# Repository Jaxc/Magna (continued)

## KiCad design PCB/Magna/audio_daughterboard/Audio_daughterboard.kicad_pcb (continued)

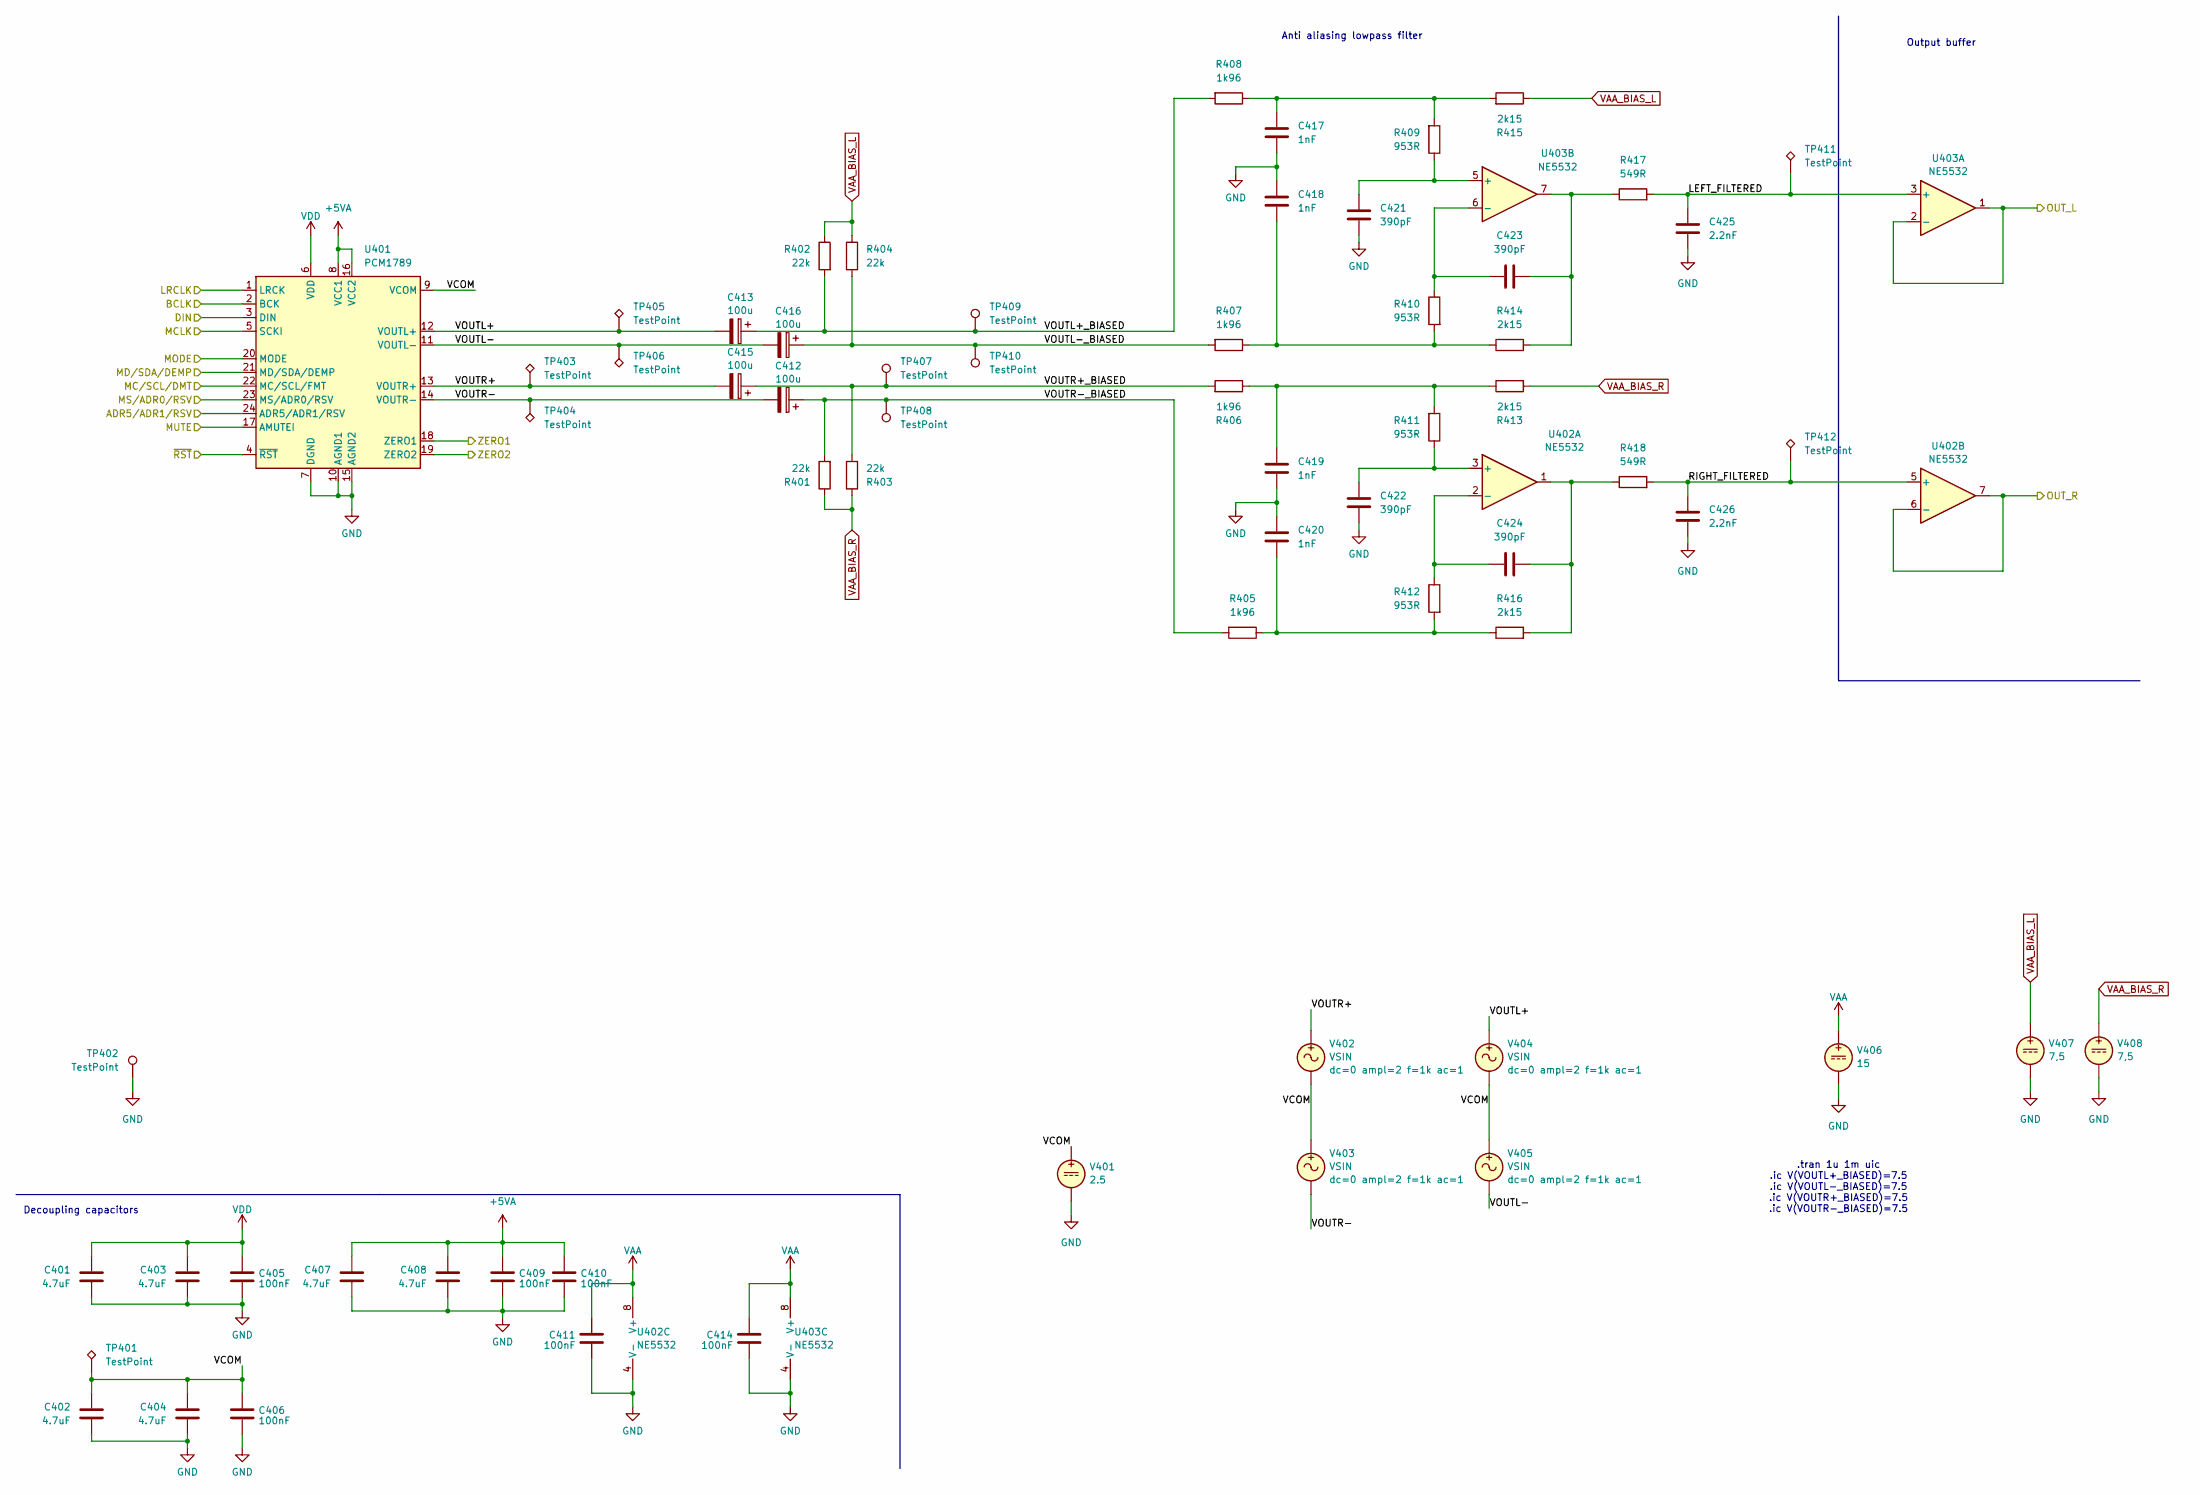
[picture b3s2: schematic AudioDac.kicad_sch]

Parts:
C401, C402, C403, C404, C407, C408: 4.7uF; C_1206_3216Metric; LCSC C29823
C405, C406, C409, C410, C411, C414: 100nF; C_0603_1608Metric; LCSC C14663
C412, C413, C415, C416: 100u; CP_Elec_6.3x7.7; LCSC C251007
C417, C418, C419, C420: 1nF; C_0603_1608Metric; LCSC C163508
C421, C422, C423, C424: 390pF; C_0603_1608Metric; LCSC C472793
C425, C426: 2.2nF; C_0603_1608Metric; LCSC C33353
R401, R402, R403, R404: 22k; R_0603_1608Metric; LCSC C335085
R405, R406, R407, R408: 1k96; R_0603_1608Metric; LCSC C160602
R409, R410, R411, R412: 953R; R_0603_1608Metric; LCSC C311896
R413, R414, R415, R416: 2k15; R_0603_1608Metric; LCSC C667562
R417, R418: 549R; R_0603_1608Metric; LCSC C218072
TP401, TP403, TP404, TP405, TP406, TP411, TP412: TestPoint; TestPoint_Pad_1.0x1.0mm
TP402, TP407, TP408, TP409, TP410: TestPoint; TestPoint_Keystone_5005-5009_Compact
U401: PCM1789; TSSOP-24_4.4x7.8mm_P0.65mm; LCSC C962089
U402, U403: NE5532; SOIC-8_3.9x4.9mm_P1.27mm; LCSC C7426
V401: 2.5
V402, V403, V404, V405: VSIN
V406: 15
V407, V408: 7,5

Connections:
+5VA: C407.1, C408.1, C409.1, C410.1, U401.8 (VCC1), U401.16 (VCC2); also elsewhere on the board
/AudioDac0/ADR5/ADR1/RSV: U401.24 (ADR5/ADR1/RSV); also elsewhere on the board
/AudioDac0/LEFT_FILTERED: C425.2, R417.2, TP411.1, U403.3 (+)
/AudioDac0/MC/SCL/DMT: U401.22 (MC/SCL/FMT); also elsewhere on the board
/AudioDac0/MD/SDA/DEMP: U401.21 (MD/SDA/DEMP); also elsewhere on the board
/AudioDac0/MODE: U401.20 (MODE); also elsewhere on the board
/AudioDac0/MS/ADR0/RSV: U401.23 (MS/ADR0/RSV); also elsewhere on the board
/AudioDac0/MUTE: U401.17 (AMUTEI); also elsewhere on the board
/AudioDac0/OUT_L: U403.1, U403.2 (-); also elsewhere on the board
/AudioDac0/OUT_R: U402.6 (-), U402.7; also elsewhere on the board
/AudioDac0/RIGHT_FILTERED: C426.2, R418.2, TP412.1, U402.5 (+)
/AudioDac0/VCOM: C402.1, C404.1, C406.1, TP401.1, U401.9 (VCOM)
/AudioDac0/VOUTL+: C413.2, TP405.1, U401.12 (VOUTL+)
/AudioDac0/VOUTL+_BIASED: C413.1, R402.2, R408.2, TP409.1
/AudioDac0/VOUTL-: C416.2, TP406.1, U401.11 (VOUTL-)
/AudioDac0/VOUTL-_BIASED: C416.1, R404.2, R407.2, TP410.1
/AudioDac0/VOUTR+: C415.2, TP403.1, U401.13 (VOUTR+)
/AudioDac0/VOUTR+_BIASED: C415.1, R403.2, R406.2, TP407.1
/AudioDac0/VOUTR-: C412.2, TP404.1, U401.14 (VOUTR-)
/AudioDac0/VOUTR-_BIASED: C412.1, R401.2, R405.2, TP408.1
/AudioDac0/ZERO1: U401.18 (ZERO1); also elsewhere on the board
/AudioDac0/ZERO2: U401.19 (ZERO2); also elsewhere on the board
/AudioDac0/~RST: U401.4 (~RST); also elsewhere on the board
/DAC1_BCLK: U401.2 (BCK); also elsewhere on the board
/DAC1_MCLK: U401.5 (SCKI); also elsewhere on the board
/DAC_DATA_1: U401.3 (DIN); also elsewhere on the board
/LRCLK: U401.1 (LRCK); also elsewhere on the board
GND: C401.2, C402.2, C403.2, C404.2, C405.2, C406.2, C407.2, C408.2, C409.2, C410.2, C411.2, C414.2, C417.2, C418.1, C419.2, C420.1, C421.2, C422.2, C425.1, C426.1, TP402.1, U401.7 (DGND), U401.10 (AGND1), U401.15 (AGND2), U402.4 (V-), U403.4 (V-), V401.2, V406.2, V407.2, V408.2; also elsewhere on the board
unnamed: C417.1, R408.1, R409.2, R415.2
unnamed: C418.2, R407.1, R410.2, R414.1
unnamed: C419.1, R406.1, R411.2, R413.1
unnamed: C420.2, R405.1, R412.2, R416.1
unnamed: C423.2, R414.2, R417.1, U403.7
unnamed: C424.2, R416.2, R418.1, U402.1
unnamed: C422.1, R411.1, U402.3 (+)
unnamed: C424.1, R412.1, U402.2 (-)
unnamed: C421.1, R409.1, U403.5 (+)
unnamed: C423.1, R410.1, U403.6 (-)
VAA: C411.1, C414.1, U402.8 (V+), U403.8 (V+), V406.1; also elsewhere on the board
VAA_BIAS_L: R402.1, R404.1, R415.1, V407.1; also elsewhere on the board
VAA_BIAS_R: R401.1, R403.1, R413.2, V408.1; also elsewhere on the board
VDD: C401.1, C403.1, C405.1, U401.6 (VDD); also elsewhere on the board

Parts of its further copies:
C501, C502, C503, C504, C507, C508: 4.7uF; C_1206_3216Metric; LCSC C29823
C505, C506, C509, C510, C511, C514: 100nF; C_0603_1608Metric; LCSC C14663
C512, C513, C515, C516: 100u; CP_Elec_6.3x7.7; LCSC C251007
C517, C518, C519, C520: 1nF; C_0603_1608Metric; LCSC C163508
C521, C522, C523, C524: 390pF; C_0603_1608Metric; LCSC C472793
C525, C526: 2.2nF; C_0603_1608Metric; LCSC C33353
R501, R502, R503, R504: 22k; R_0603_1608Metric; LCSC C335085
R505, R506, R507, R508: 1k96; R_0603_1608Metric; LCSC C160602
R509, R510, R511, R512: 953R; R_0603_1608Metric; LCSC C311896
R513, R514, R515, R516: 2k15; R_0603_1608Metric; LCSC C667562
R517, R518: 549R; R_0603_1608Metric; LCSC C218072
TP501, TP503, TP504, TP505, TP506, TP511, TP512: TestPoint; TestPoint_Pad_1.0x1.0mm
TP502, TP507, TP508, TP509, TP510: TestPoint; TestPoint_Keystone_5005-5009_Compact
U501: PCM1789; TSSOP-24_4.4x7.8mm_P0.65mm; LCSC C962089
U502, U503: NE5532; SOIC-8_3.9x4.9mm_P1.27mm; LCSC C7426

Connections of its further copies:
+5VA: C507.1, C508.1, C509.1, C510.1, U501.8 (VCC1), U501.16 (VCC2); also elsewhere on the board
/AudioDac0/MC/SCL/DMT: U501.22 (MC/SCL/FMT); also elsewhere on the board
/AudioDac0/MD/SDA/DEMP: U501.21 (MD/SDA/DEMP); also elsewhere on the board
/AudioDac0/MUTE: U501.17 (AMUTEI); also elsewhere on the board
/AudioDac0/~RST: U501.4 (~RST); also elsewhere on the board
/AudioDac1/ADR5/ADR1/RSV: U501.24 (ADR5/ADR1/RSV); also elsewhere on the board
/AudioDac1/LEFT_FILTERED: C525.2, R517.2, TP511.1, U503.3 (+)
/AudioDac1/MODE: U501.20 (MODE); also elsewhere on the board
/AudioDac1/MS/ADR0/RSV: U501.23 (MS/ADR0/RSV); also elsewhere on the board
/AudioDac1/OUT_L: U503.1, U503.2 (-); also elsewhere on the board
/AudioDac1/OUT_R: U502.6 (-), U502.7; also elsewhere on the board
/AudioDac1/RIGHT_FILTERED: C526.2, R518.2, TP512.1, U502.5 (+)
/AudioDac1/VCOM: C502.1, C504.1, C506.1, TP501.1, U501.9 (VCOM)
/AudioDac1/VOUTL+: C513.2, TP505.1, U501.12 (VOUTL+)
/AudioDac1/VOUTL+_BIASED: C513.1, R502.2, R508.2, TP509.1
/AudioDac1/VOUTL-: C516.2, TP506.1, U501.11 (VOUTL-)
/AudioDac1/VOUTL-_BIASED: C516.1, R504.2, R507.2, TP510.1
/AudioDac1/VOUTR+: C515.2, TP503.1, U501.13 (VOUTR+)
/AudioDac1/VOUTR+_BIASED: C515.1, R503.2, R506.2, TP507.1
/AudioDac1/VOUTR-: C512.2, TP504.1, U501.14 (VOUTR-)
/AudioDac1/VOUTR-_BIASED: C512.1, R501.2, R505.2, TP508.1
/AudioDac1/ZERO1: U501.18 (ZERO1); also elsewhere on the board
/AudioDac1/ZERO2: U501.19 (ZERO2); also elsewhere on the board
/DAC0_BCLK: U501.2 (BCK); also elsewhere on the board
/DAC0_MCLK: U501.5 (SCKI); also elsewhere on the board
/DAC_DATA_0: U501.3 (DIN); also elsewhere on the board
/LRCLK: U501.1 (LRCK); also elsewhere on the board
GND: C501.2, C502.2, C503.2, C504.2, C505.2, C506.2, C507.2, C508.2, C509.2, C510.2, C511.2, C514.2, C517.2, C518.1, C519.2, C520.1, C521.2, C522.2, C525.1, C526.1, TP502.1, U501.7 (DGND), U501.10 (AGND1), U501.15 (AGND2), U502.4 (V-), U503.4 (V-); also elsewhere on the board
unnamed: C517.1, R508.1, R509.2, R515.2
unnamed: C518.2, R507.1, R510.2, R514.1
unnamed: C519.1, R506.1, R511.2, R513.1
unnamed: C520.2, R505.1, R512.2, R516.1
unnamed: C523.2, R514.2, R517.1, U503.7
unnamed: C524.2, R516.2, R518.1, U502.1
unnamed: C522.1, R511.1, U502.3 (+)
unnamed: C524.1, R512.1, U502.2 (-)
unnamed: C521.1, R509.1, U503.5 (+)
unnamed: C523.1, R510.1, U503.6 (-)
VAA: C511.1, C514.1, U502.8 (V+), U503.8 (V+); also elsewhere on the board
VAA_BIAS_L: R502.1, R504.1, R515.1; also elsewhere on the board
VAA_BIAS_R: R501.1, R503.1, R513.2; also elsewhere on the board
VDD: C501.1, C503.1, C505.1, U501.6 (VDD); also elsewhere on the board

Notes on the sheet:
Decoupling capacitors
Output buffer
.tran 1u 1m uic .ic V(VOUTL+_BIASED)=7.5 .ic V(VOUTL-_BIASED)=7.5 .ic V(VOUTR+_BIASED)=7.5 .ic V(VOUTR-_BIASED)=7.5
Anti aliasing lowpass filter

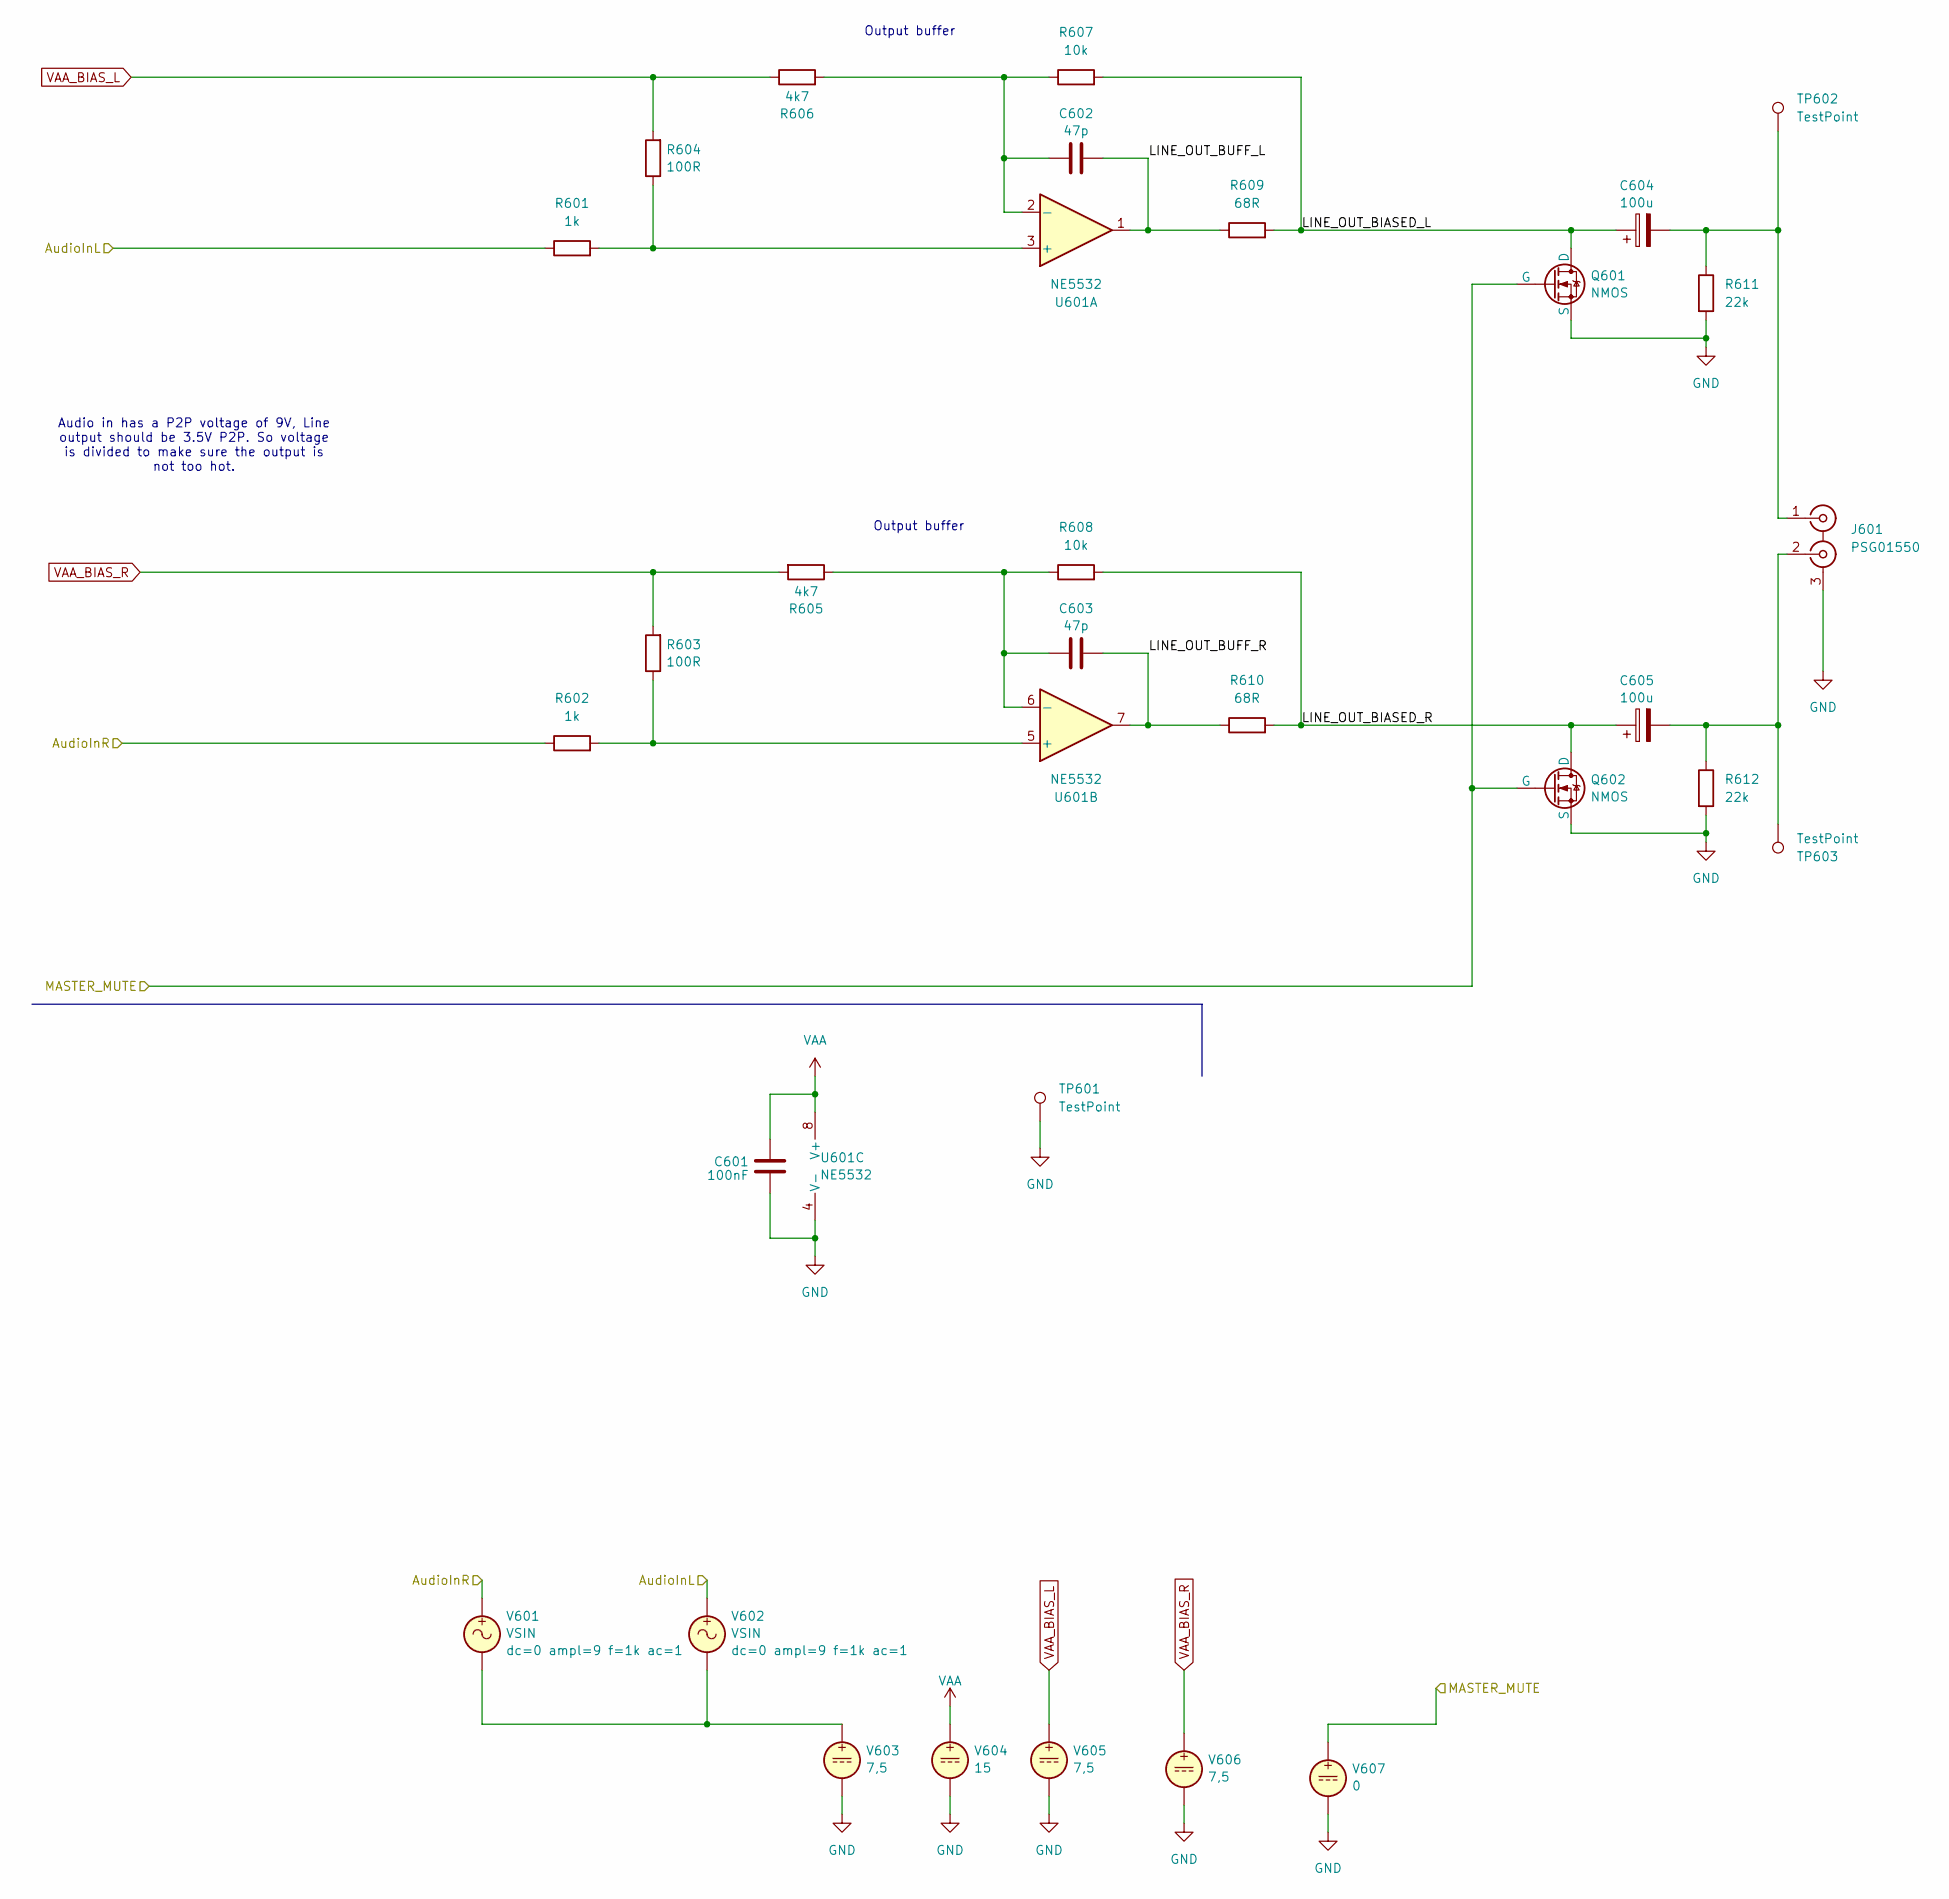
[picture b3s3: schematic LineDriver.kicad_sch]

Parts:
C601: 100nF; C_0603_1608Metric; LCSC C14663
C602, C603: 47p; C_0603_1608Metric; LCSC C1671
C604, C605: 100u; CP_Elec_6.3x7.7; LCSC C251007
J601: PSG01550; psg01550
Q601, Q602: NMOS; SOT-23-3; LCSC C20917
R601, R602: 1k; R_0603_1608Metric; LCSC C110776
R603, R604: 100R; R_0603_1608Metric; LCSC C122970
R605, R606: 4k7; R_0603_1608Metric; LCSC C2989582
R607, R608: 10k; R_0603_1608Metric; LCSC C95204
R609, R610: 68R; R_0603_1608Metric; LCSC C351632
R611, R612: 22k; R_0603_1608Metric; LCSC C335085
TP601, TP602, TP603: TestPoint; TestPoint_Keystone_5005-5009_Compact
U601: NE5532; SOIC-8_3.9x4.9mm_P1.27mm; LCSC C7426
V601, V602: VSIN
V603, V605, V606: 7,5
V604: 15
V607: 0

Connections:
/AudioDac0/OUT_L: R601.1, V602.1; also elsewhere on the board
/AudioDac0/OUT_R: R602.1, V601.1; also elsewhere on the board
/Config MCU/LINE_MUTE: Q601.2 (G), Q602.2 (G), V607.1; also elsewhere on the board
/Line Driver/LINE_OUT_BIASED_L: C604.1, Q601.1 (D), R607.2, R609.2
/Line Driver/LINE_OUT_BIASED_R: C605.1, Q602.1 (D), R608.2, R610.2
/Line Driver/LINE_OUT_BUFF_L: C602.2, R609.1, U601.1
/Line Driver/LINE_OUT_BUFF_R: C603.2, R610.1, U601.7
GND: C601.2, J601.3 (EXT), Q601.3 (S), Q602.3 (S), R611.2, R612.2, TP601.1, U601.4 (V-), V603.2, V604.2, V605.2, V606.2, V607.2; also elsewhere on the board
unnamed: C604.2, J601.1 (IN1), R611.1, TP602.1
unnamed: C605.2, J601.2 (IN2), R612.1, TP603.1
unnamed: R601.2, R604.1, U601.3 (+)
unnamed: C602.1, R606.2, R607.1, U601.2 (-)
unnamed: R602.2, R603.1, U601.5 (+)
unnamed: C603.1, R605.1, R608.1, U601.6 (-)
unnamed: V601.2, V602.2, V603.1
VAA: C601.1, U601.8 (V+), V604.1; also elsewhere on the board
VAA_BIAS_L: R604.2, R606.1, V605.1; also elsewhere on the board
VAA_BIAS_R: R603.2, R605.2, V606.1; also elsewhere on the board

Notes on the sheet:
Output buffer
Audio in has a P2P voltage of 9V, Line output should be 3.5V P2P. So voltage is divided to make sure the output is not too hot.

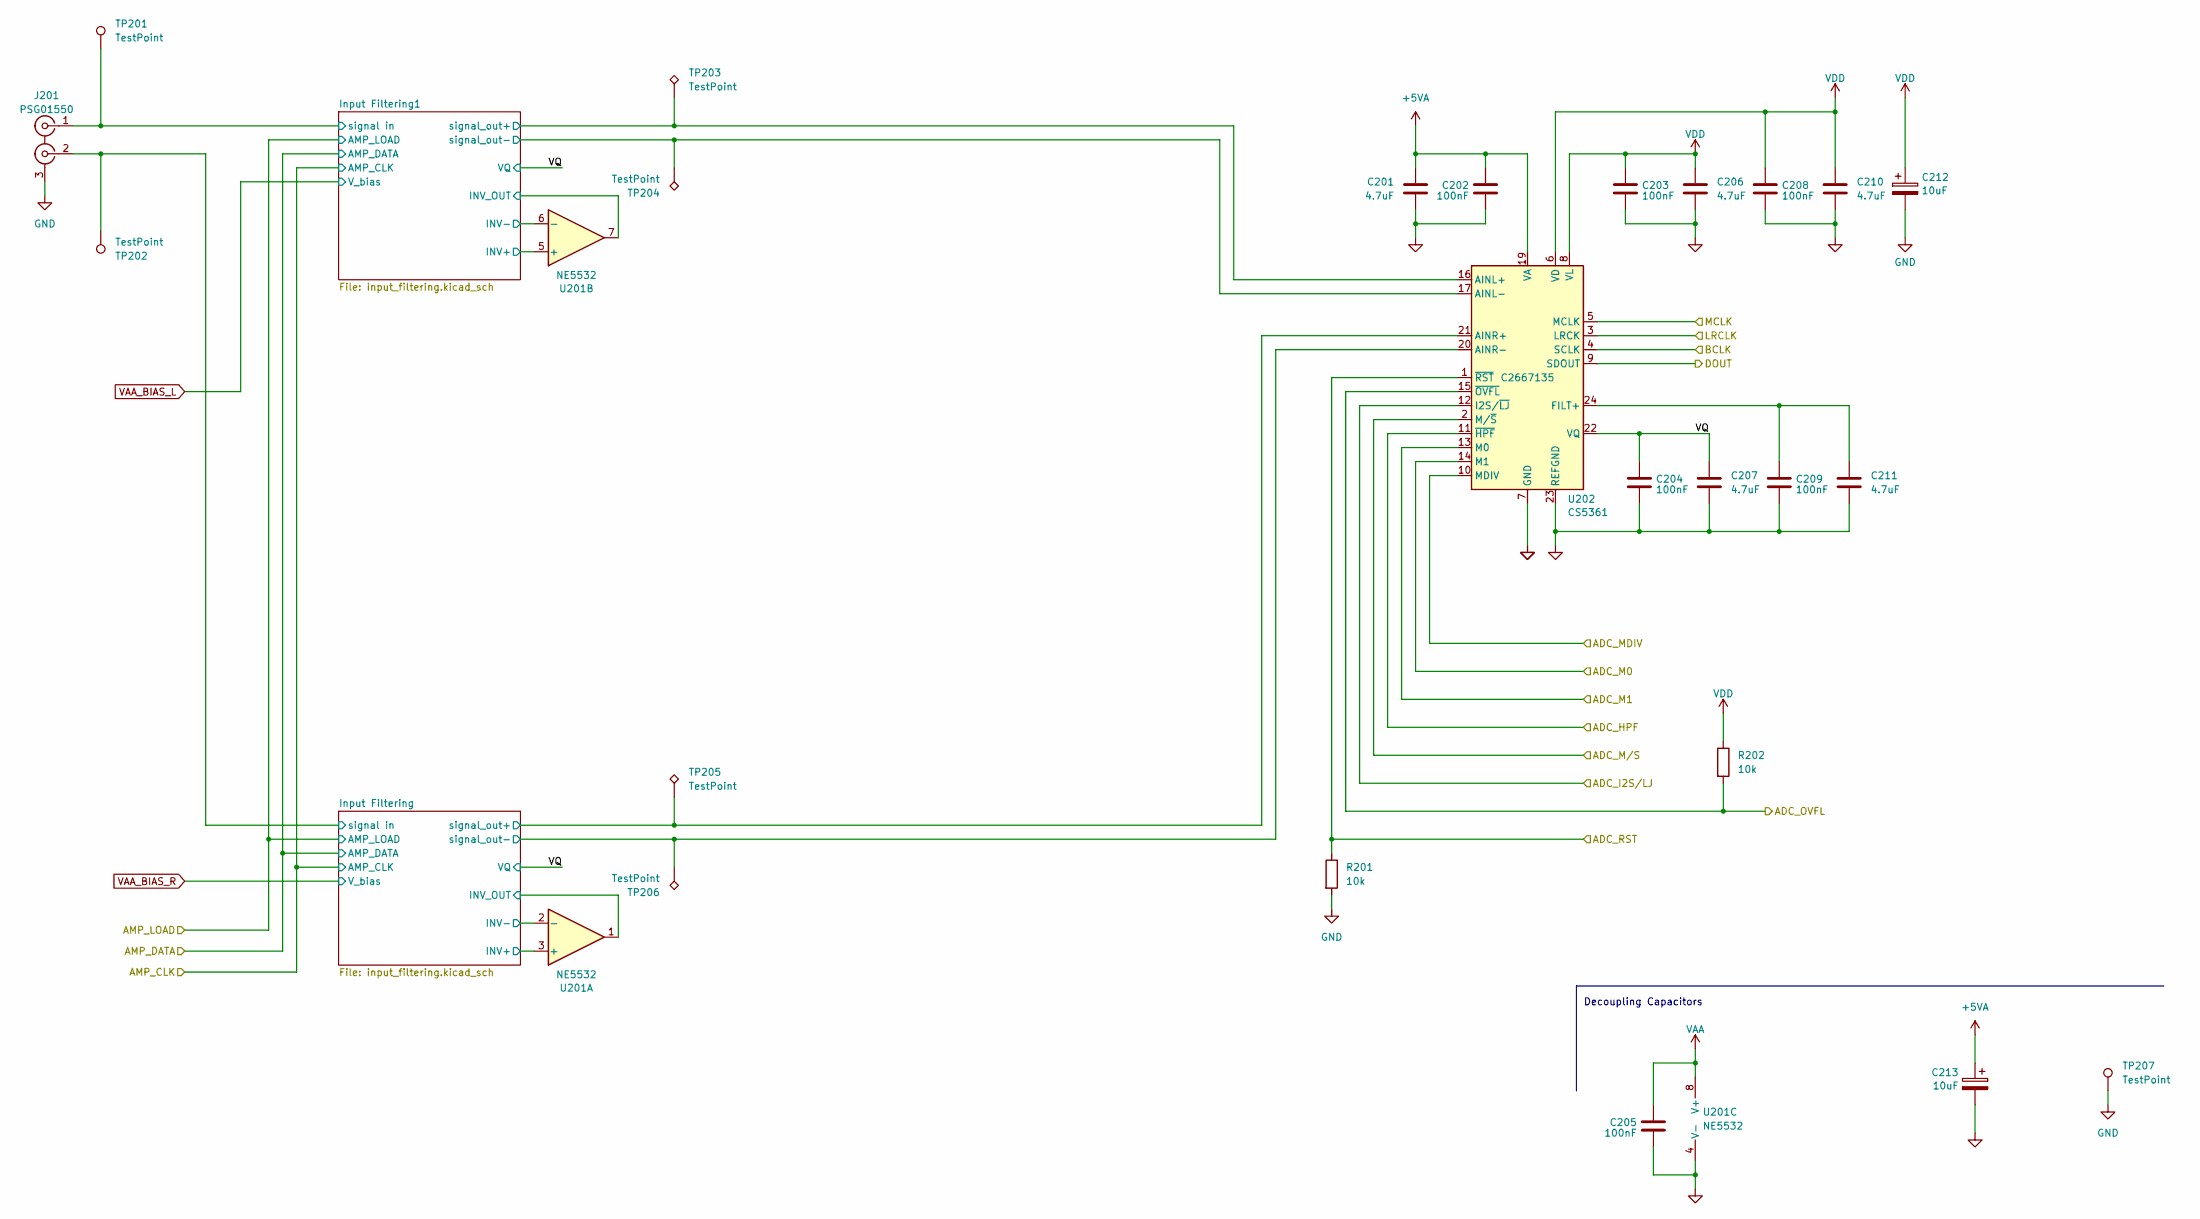
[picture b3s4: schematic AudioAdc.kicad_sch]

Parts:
C201, C206, C207, C210, C211: 4.7uF; C_1206_3216Metric; LCSC C29823
C202, C203, C204, C205, C208, C209: 100nF; C_0603_1608Metric; LCSC C14663
C212, C213: 10uF; CP_Elec_4x5.8; LCSC C2163094
J201: PSG01550; psg01550
R201, R202: 10k; R_0603_1608Metric; LCSC C95204
TP201, TP202, TP207: TestPoint; TestPoint_Keystone_5005-5009_Compact
TP203, TP204, TP205, TP206: TestPoint; TestPoint_Pad_1.0x1.0mm
U201: NE5532; SOIC-8_3.9x4.9mm_P1.27mm; LCSC C7426
U202: CS5361; SOIC-24W_7.5x15.4mm_P1.27mm; LCSC C2667135

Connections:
+5VA: C201.1, C202.1, C213.1, U202.19 (VA); also elsewhere on the board
/ADC0_BCLK: U202.4 (SCLK); also elsewhere on the board
/ADC0_MCLK: U202.5 (MCLK); also elsewhere on the board
/ADC_DATA_0: U202.9 (SDOUT); also elsewhere on the board
/AudioAdc0/ADC_HPF: U202.11 (~HPF); also elsewhere on the board
/AudioAdc0/ADC_I2S/LJ: U202.12 (I2S/~LJ); also elsewhere on the board
/AudioAdc0/ADC_M0: U202.14 (M1); also elsewhere on the board
/AudioAdc0/ADC_M1: U202.13 (M0); also elsewhere on the board
/AudioAdc0/ADC_MDIV: U202.10 (MDIV); also elsewhere on the board
/AudioAdc0/ADC_M/S: U202.2 (M/~S); also elsewhere on the board
/AudioAdc0/ADC_OVFL: R202.2, U202.15 (~OVFL); also elsewhere on the board
/AudioAdc0/ADC_RST: R201.1, U202.1 (~RST); also elsewhere on the board
/AudioAdc0/Input Filtering1/INV-: U201.6 (-); also elsewhere on the board
/AudioAdc0/Input Filtering1/INV_OUT: U201.7; also elsewhere on the board
/AudioAdc0/Input Filtering1/signal in: J201.1 (IN1), TP201.1; also elsewhere on the board
/AudioAdc0/Input Filtering1/signal_out+: TP203.1, U202.16 (AINL+); also elsewhere on the board
/AudioAdc0/Input Filtering1/signal_out-: TP204.1, U202.17 (AINL-); also elsewhere on the board
/AudioAdc0/Input Filtering/INV-: U201.2 (-); also elsewhere on the board
/AudioAdc0/Input Filtering/INV_OUT: U201.1; also elsewhere on the board
/AudioAdc0/Input Filtering/signal in: J201.2 (IN2), TP202.1; also elsewhere on the board
/AudioAdc0/Input Filtering/signal_out+: TP205.1, U202.21 (AINR+); also elsewhere on the board
/AudioAdc0/Input Filtering/signal_out-: TP206.1, U202.20 (AINR-); also elsewhere on the board
/AudioAdc0/VQ: C204.1, C207.1, U202.22 (VQ); also elsewhere on the board
/LRCLK: U202.3 (LRCK); also elsewhere on the board
GND: C201.2, C202.2, C203.2, C204.2, C205.2, C206.2, C207.2, C208.2, C209.2, C210.2, C211.2, C212.2, C213.2, J201.3 (EXT), R201.2, TP207.1, U201.4 (V-), U202.7 (GND), U202.18 (GND), U202.23 (REFGND); also elsewhere on the board
unnamed: C209.1, C211.1, U202.24 (FILT+)
VAA: C205.1, U201.8 (V+); also elsewhere on the board
VAA_BIAS_L: U201.5 (+); also elsewhere on the board
VAA_BIAS_R: U201.3 (+); also elsewhere on the board
VDD: C203.1, C206.1, C208.1, C210.1, C212.1, R202.1, U202.6 (VD), U202.8 (VL); also elsewhere on the board

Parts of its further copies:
C301, C306, C307, C310, C311: 4.7uF; C_1206_3216Metric; LCSC C29823
C302, C303, C304, C305, C308, C309: 100nF; C_0603_1608Metric; LCSC C14663
C312, C313: 10uF; CP_Elec_4x5.8; LCSC C2163094
J301: PSG01550; psg01550
R301, R302: 10k; R_0603_1608Metric; LCSC C95204
TP301, TP302, TP307: TestPoint; TestPoint_Keystone_5005-5009_Compact
TP303, TP304, TP305, TP306: TestPoint; TestPoint_Pad_1.0x1.0mm
U301: NE5532; SOIC-8_3.9x4.9mm_P1.27mm; LCSC C7426
U302: CS5361; SOIC-24W_7.5x15.4mm_P1.27mm; LCSC C2667135

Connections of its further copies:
+5VA: C301.1, C302.1, C313.1, U302.19 (VA); also elsewhere on the board
/ADC1_BCLK: U302.4 (SCLK); also elsewhere on the board
/ADC1_MCLK: U302.5 (MCLK); also elsewhere on the board
/ADC_DATA_1: U302.9 (SDOUT); also elsewhere on the board
/AudioAdc0/ADC_HPF: U302.11 (~HPF); also elsewhere on the board
/AudioAdc0/ADC_I2S/LJ: U302.12 (I2S/~LJ); also elsewhere on the board
/AudioAdc0/ADC_M0: U302.14 (M1); also elsewhere on the board
/AudioAdc0/ADC_M1: U302.13 (M0); also elsewhere on the board
/AudioAdc0/ADC_MDIV: U302.10 (MDIV); also elsewhere on the board
/AudioAdc0/ADC_M/S: U302.2 (M/~S); also elsewhere on the board
/AudioAdc0/ADC_RST: R301.1, U302.1 (~RST); also elsewhere on the board
/AudioAdc1/ADC_OVFL: R302.2, U302.15 (~OVFL); also elsewhere on the board
/AudioAdc1/Input Filtering1/INV-: U301.6 (-); also elsewhere on the board
/AudioAdc1/Input Filtering1/INV_OUT: U301.7; also elsewhere on the board
/AudioAdc1/Input Filtering1/signal in: J301.1 (IN1), TP301.1; also elsewhere on the board
/AudioAdc1/Input Filtering1/signal_out+: TP303.1, U302.16 (AINL+); also elsewhere on the board
/AudioAdc1/Input Filtering1/signal_out-: TP304.1, U302.17 (AINL-); also elsewhere on the board
/AudioAdc1/Input Filtering/INV-: U301.2 (-); also elsewhere on the board
/AudioAdc1/Input Filtering/INV_OUT: U301.1; also elsewhere on the board
/AudioAdc1/Input Filtering/signal in: J301.2 (IN2), TP302.1; also elsewhere on the board
/AudioAdc1/Input Filtering/signal_out+: TP305.1, U302.21 (AINR+); also elsewhere on the board
/AudioAdc1/Input Filtering/signal_out-: TP306.1, U302.20 (AINR-); also elsewhere on the board
/AudioAdc1/VQ: C304.1, C307.1, U302.22 (VQ); also elsewhere on the board
/LRCLK: U302.3 (LRCK); also elsewhere on the board
GND: C301.2, C302.2, C303.2, C304.2, C305.2, C306.2, C307.2, C308.2, C309.2, C310.2, C311.2, C312.2, C313.2, J301.3 (EXT), R301.2, TP307.1, U301.4 (V-), U302.7 (GND), U302.18 (GND), U302.23 (REFGND); also elsewhere on the board
unnamed: C309.1, C311.1, U302.24 (FILT+)
VAA: C305.1, U301.8 (V+); also elsewhere on the board
VAA_BIAS_L: U301.5 (+); also elsewhere on the board
VAA_BIAS_R: U301.3 (+); also elsewhere on the board
VDD: C303.1, C306.1, C308.1, C310.1, C312.1, R302.1, U302.6 (VD), U302.8 (VL); also elsewhere on the board

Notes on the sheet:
Decoupling Capacitors
